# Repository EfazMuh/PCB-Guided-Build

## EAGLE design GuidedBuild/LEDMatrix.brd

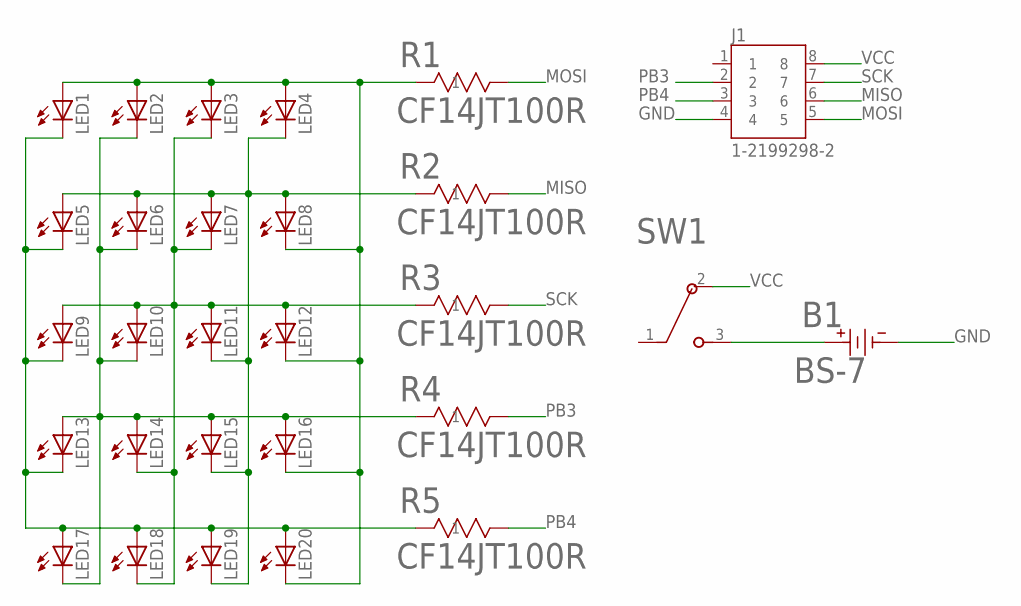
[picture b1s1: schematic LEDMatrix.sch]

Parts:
B1: BS-7; BS-7_MPD
J1: 1-2199298-2; TE_1-2199298-2
LED1, LED2, LED3, LED4, LED5, LED6, LED7, LED8, LED9, LED10, LED11, LED12, LED13, LED14, LED15, LED16, LED17, LED18, LED19, LED20: LED3MM
R1, R2, R3, R4, R5: CF14JT100R; STA_CF14_STP
SW1: EG1218; SW_1218_EWI

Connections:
GND: B1.1, J1.4
MISO: J1.6, R2.2
MOSI: J1.5, R1.2
unnamed: LED1.A, LED2.A, LED3.A, LED4.A, LED8.K (C), LED12.K (C), LED16.K (C), LED20.K (C), R1.1
unnamed: LED4.K (C), LED5.A, LED6.A, LED7.A, LED8.A, LED11.K (C), LED15.K (C), LED19.K (C), R2.1
unnamed: LED3.K (C), LED7.K (C), LED9.A, LED10.A, LED11.A, LED12.A, LED14.K (C), LED18.K (C), R3.1
unnamed: LED2.K (C), LED6.K (C), LED10.K (C), LED13.A, LED14.A, LED15.A, LED16.A, LED17.K (C), R4.1
unnamed: LED1.K (C), LED5.K (C), LED9.K (C), LED13.K (C), LED17.A, LED18.A, LED19.A, LED20.A, R5.1
unnamed: B1.2, SW1.3
PB3: J1.2, R4.2
PB4: J1.3, R5.2
SCK: J1.7, R3.2
VCC: J1.8, SW1.2

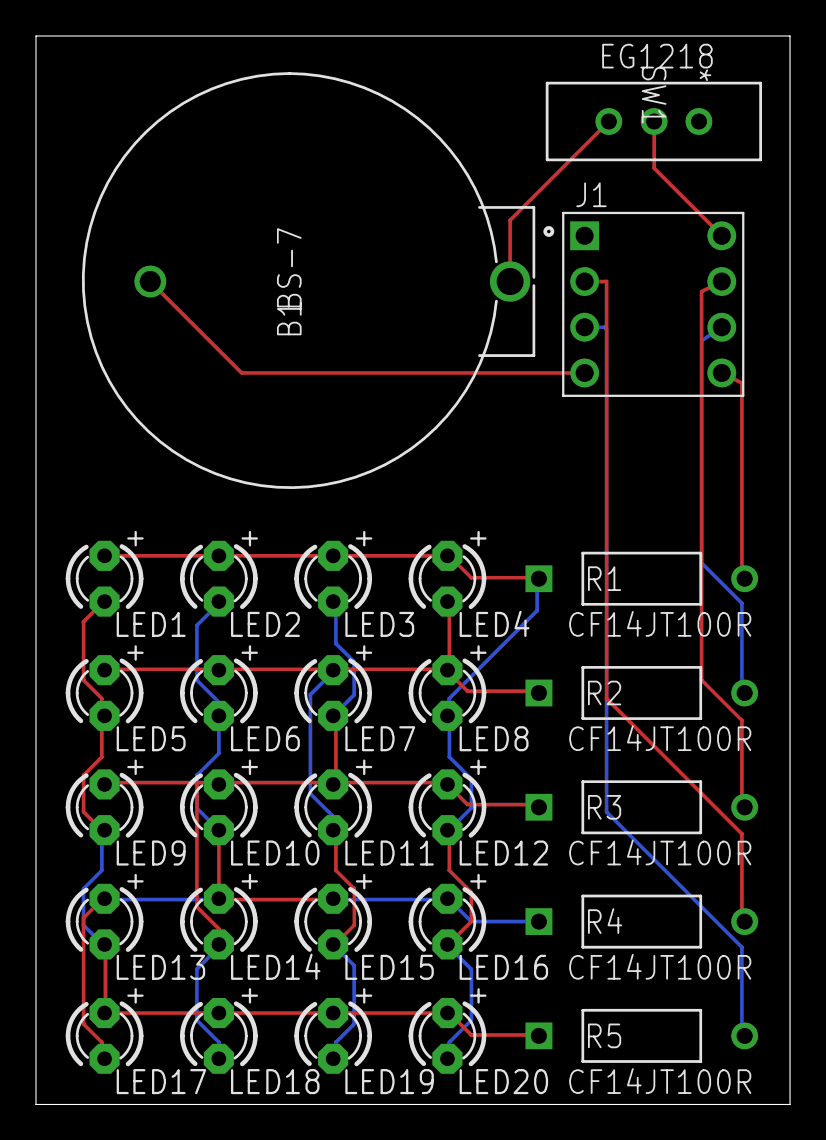
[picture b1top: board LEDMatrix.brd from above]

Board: 2 copper layers, 41.9 x 59.4 mm, 28 parts (0 on the bottom side), 13 nets.

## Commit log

2020-10-25 Corrected files
2020-11-01 Added more files
2020-11-04 Added sample board
2020-11-14 Added LEDMatrix code

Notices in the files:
parts and their libraries:
COPYRIGHT: Copyright (C) 2018 Accelerated Designs. All rights reserved
SparkFun-Aesthetics: Licensing: Creative Commons ShareAlike 4.0 International - https://creativecommons.org/licenses/by-sa/4.0
SparkFun-Aesthetics: Released under the Creative Commons Attribution Share-Alike 4.0 License
